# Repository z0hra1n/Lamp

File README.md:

This is a 3d printed adjustable diffusion lamp with an esp32 and turns on and off according to time.

I made this project because i desparately needed funds for my visa.

This project got rejected as t1 before so i made a pcb and now hopefully it gets approved as t2.

# Bill of Materials (BOM)

Name                | Purpose                                   | Quantity | Total Cost (USD) | Link                                                                 | Distributor
--------------------|-------------------------------------------|----------|------------------|----------------------------------------------------------------------|------------
Solder iron kit     | for soldering the pcb components together | 1        | 9.80             | https://www.amazon.in/Party-Adjustable-Temperature-Soldering-Electronics/dp/B0DJV6MZFV | Amazon
PCB                 | for avoiding wires                        | 1        | 8.71             | https://zbotic.in/pcb-manufacturing/                                 | zbotic
MOSFET              | for controlling the light through esp32   | 5        | 2.80             | https://robu.in/product/irlz44npbf-hxy-mosfet-60v-60a-120w-12m%cf%8910v25a-4v-1-n-channel-to-220-mosfets-rohs/ | robu.in
ESP32 XIAO          | for controlling the light                 | 1        | 10.18            | https://robocraze.com/products/seeed-studio-xiao-esp32-s3-development-board-supports-wi-fi-bluetooth-5-0 | robocraze
3D printed parts    | for the lamp's structure                  | 1        | 5.00             | https://printlegion.hackclub.com/                                    | printing legion
LED strip (5V)      | for light                                | 1        | 2.14             | https://www.amazon.in/CBK-Flexible-Multicolor-Background-Controller/dp/B0F8BVLXBJ | Amazon

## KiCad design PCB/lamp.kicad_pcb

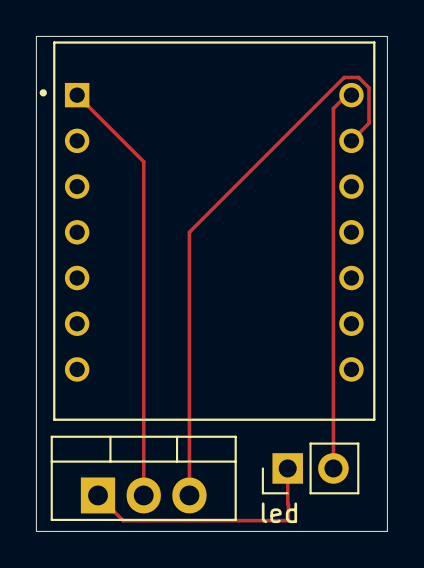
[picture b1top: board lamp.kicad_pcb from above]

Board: 2 copper layers, 19.5 x 27.5 mm, 3 parts (0 on the bottom side), 4 nets.

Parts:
Q1: NMOS; TO-220-3_Vertical
U1: XIAO_ESP32C3; xiao
led: Conn_01x02_Pin; PinHeader_1x02_P2.54mm_Vertical

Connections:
unnamed: Q1.1 (D), led.1
unnamed: Q1.2 (G), U1.1 (D0)
unnamed: Q1.3 (S), U1.13 (GND)
unnamed: U1.14 (VUSB), led.2

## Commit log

2026-04-04 Add component table with costs and suppliers
2026-04-11 Rename LAMP-bom (1).csv to LAMP-bom.csv
2026-04-11 Add WiFi setup and LED control based on time
    Initialize WiFi connection and control LED based on time.
2026-04-11 Rename LAMP-bom (2).csv to LAMP-bom.csv
2026-04-18 Rename LAMP-bom (3).csv to LAMP-bom.csv
2026-04-18 Revise Bill of Materials with additional components
    Updated the Bill of Materials section to include new components and their details.
